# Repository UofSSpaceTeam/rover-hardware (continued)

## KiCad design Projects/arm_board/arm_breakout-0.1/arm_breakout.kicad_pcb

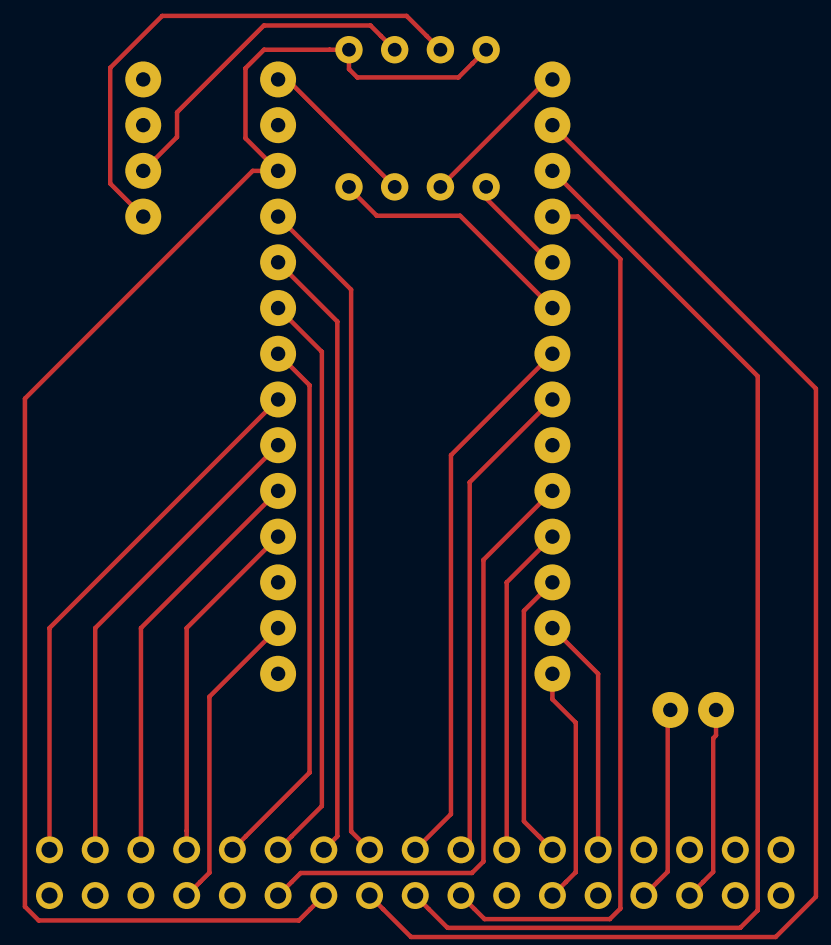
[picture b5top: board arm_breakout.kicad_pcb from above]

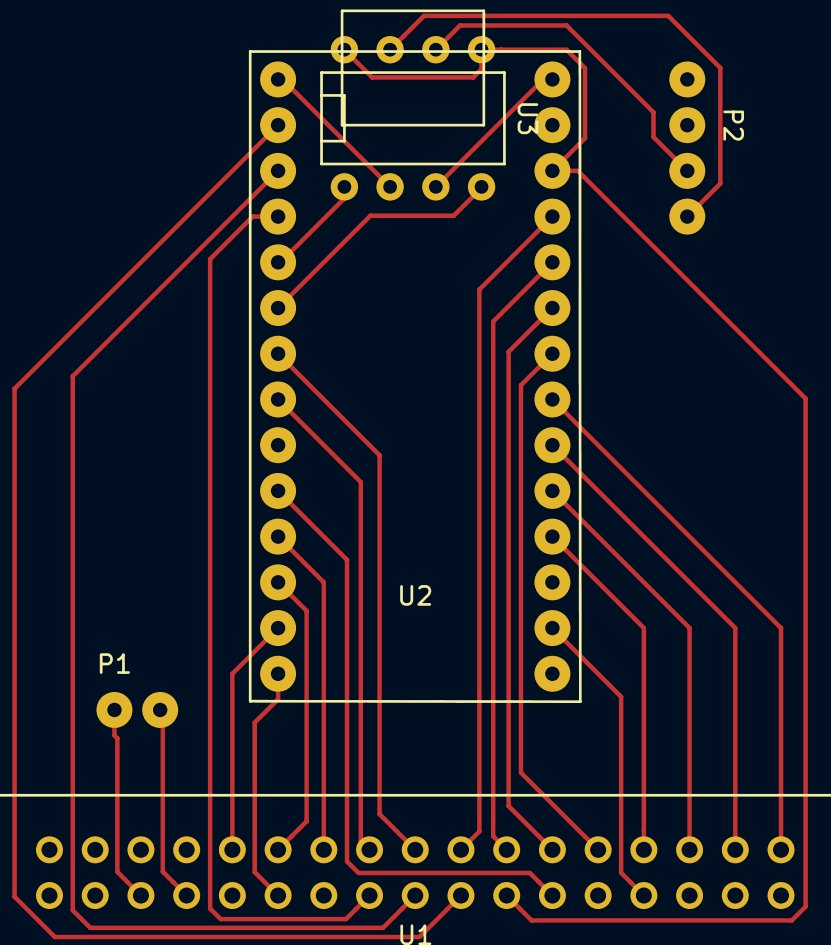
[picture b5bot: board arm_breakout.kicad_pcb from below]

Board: 2 copper layers, 5 parts (5 on the bottom side), 31 nets.

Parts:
P1: CONN_2; 2-pin-connector
P2: CONN_4; 4-pin_connector
U1: 2534-6002UB_34-pin_header; 34-pin_2534-6002UB_WIDE
U2: Teensy3.1
U3: MCP2561; MCP2562_dip

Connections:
5V: P2.4, U2.28, U3.3
/ADC_FS: U1.14, U2.26, U3.5, U3.8
/ADC_SCLK: U1.8, U2.16
/CAN_H: P2.1, U3.7
/CAN_L: P2.2, U3.6
/CNT_S0: U1.1, U2.21
/CNT_S1: U1.3, U2.20
/CNT_S2: U1.5, U2.19
/CNT_S3: U1.7, U2.18
/MCU_PWM0: U1.9, U2.22
/MCU_PWM1: U1.11, U2.23
/MCU_PWM2: U1.13, U2.24
/MCU_PWM3: U1.15, U2.25
/MCU_PWM4: U1.17, U2.7
/MCU_PWM5: U1.19, U2.8
/MCU_PWM6: U1.21, U2.11
/MCU_PWM7: U1.23, U2.12
/MCU_SDI: U1.12, U2.10
/MCU_SDO: U1.10, U2.9
/MTR_DATA: U1.4, U2.15
/MTR_EN: U1.2, U2.17
/Q_CNT: U1.25, U2.13
/SEL0: U1.16, U2.2
/SEL1: U1.18, U2.3
/SEL2: U1.20, U2.4
/WHIPER_GND: P1.1, U1.28, U2.27
/WHIPER_V++: P1.2, U1.30
/n_ADC_CS: U1.24, U2.14
GND: P2.3, U2.1, U3.2
unnamed: U2.5, U3.1
unnamed: U2.6, U3.4
